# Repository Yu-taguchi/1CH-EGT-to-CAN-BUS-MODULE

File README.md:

# 1CH EGT TO CAN BUS モジュール

これは 1 チャンネル EGT ボードです。
このボードは、アフター製 エンジン コントロール ユニットと組み合わせて使用​​し、排気ガス温度を測定することを目的としています。
PCB は、1つの MAX31855 チップと ATMEGA328P に基づいています。
使用するセンサーは、ミニ K タイプ サーモカップル コネクタを備えた K タイプ EGT センサーである必要があります。

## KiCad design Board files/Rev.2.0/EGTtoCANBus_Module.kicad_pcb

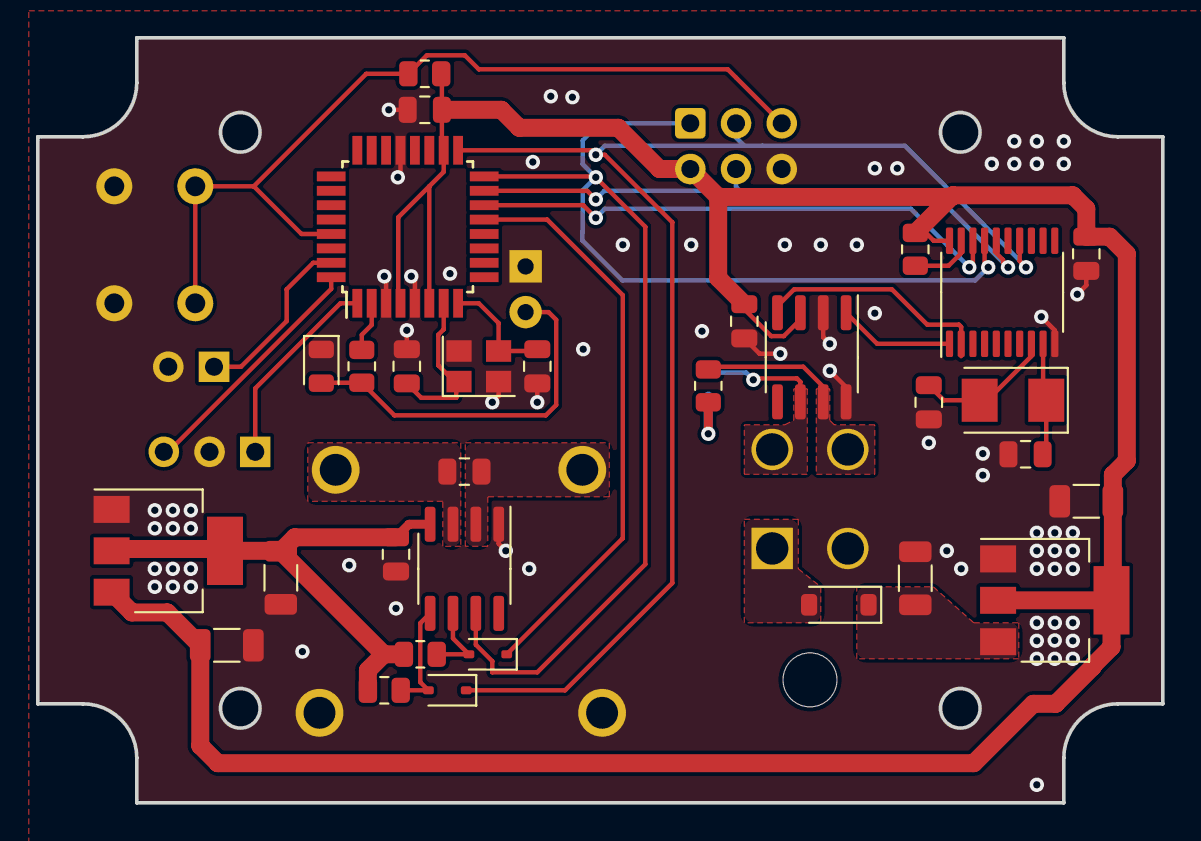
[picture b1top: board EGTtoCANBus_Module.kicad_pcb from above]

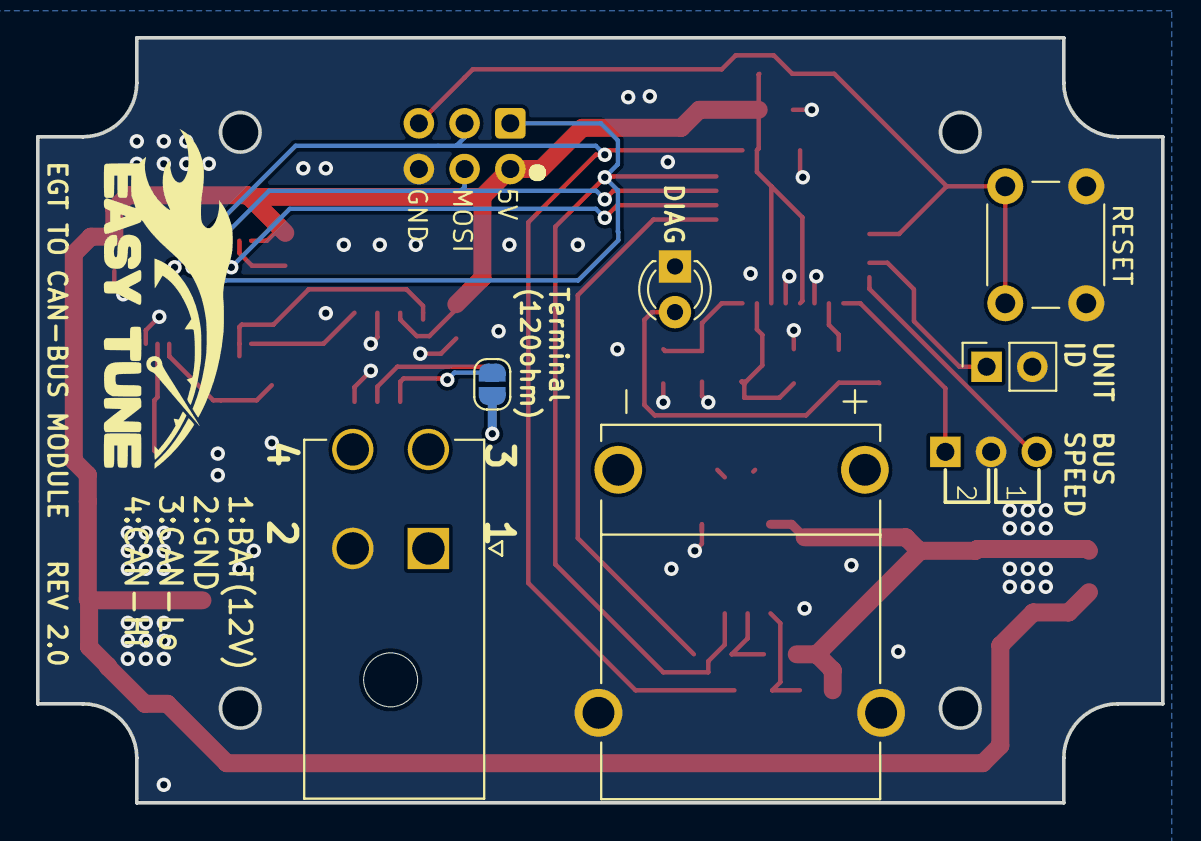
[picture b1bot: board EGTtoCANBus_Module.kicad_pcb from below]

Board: 2 copper layers, 62.5 x 42.5 mm, 39 parts (8 on the bottom side), 30 nets.

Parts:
C1, C2, C3, C8, C11: 0.1uF; C_0805_2012Metric
C4, C5, C6, C7: 10uF; C_1206_3216Metric
C9, C10, C12, C13: 22pF; C_0805_2012Metric
D1: LED; LED_D3.0mm
D2, D4: 1N4148WS; D_SOD-323
D3: D_Schottky; D_SOD-123
D5: LED; LED_0805_2012Metric
J1: AVR-ISP-6; IDC-Header_2x03_P2.54mm_Vertical
J2: 39-30-1040; MOLEX_39-30-1040
J3: PCC-SMP-V-K-5; OMEGA_PCC-SMP-K-5
JP1: SolderJumper; SolderJumper-2_P1.3mm_Open_RoundedPad1.0x1.5mm
JP2: Jumper_3_Open; PinSocket_1x03_P2.54mm_Vertical
JP3: Jumper_2_Open; PinSocket_1x02_P2.54mm_Vertical
R1: 120; R_0805_2012Metric
R2, R3, R6: 10k; R_0805_2012Metric
R5, R7: 1k; R_0805_2012Metric
RESET: SW_Push; SW_PUSH_6mm
U1: ATmega328P-A; TQFP-32_7x7mm_P0.8mm
U2: MCP2515-I; TSSOP-20_4.4x6.5mm_P0.65mm
U3: AMS1117-5.0; SOT-223-3_TabPin2
U5: AMS1117-3.3; SOT-223-3_TabPin2
U7: MAX31855KASA; SOIC-8_3.9x4.9mm_P1.27mm
U9: TJA1044T; SOIC-8_3.9x4.9mm_P1.27mm
Y2: 8MHz; Crystal_SMD_5032-2Pin_5.0x3.2mm
Y3: 16MHz; Crystal_SMD_3225-4Pin_3.2x2.5mm

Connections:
+3.3V: C3.1, C7.1, R2.1, R6.1, U5.2 (VO), U7.4 (V_CC)
+5V: C1.1, C2.1, C5.1, C6.1, C11.1, J1.2 (VCC), R3.1, R5.1, U1.4 (VCC), U1.6 (VCC), U1.18 (AVCC), U2.20 (VDD), U3.2 (VO), U5.3 (VI), U9.3 (VCC)
CANH: J2.4, R1.1, U9.7 (CANH)
CANL: J2.3, JP1.1 (A), U9.6 (CANL)
CS1: U1.14 (PB2), U2.18 (~CS)
CS2: D4.1 (K), U1.13 (PB1)
GND: C1.2, C2.2, C3.2, C4.2, C5.2, C6.2, C7.2, C9.2, C10.2, C11.2, C12.2, C13.2, D1.1 (K), D5.1 (K), J1.6 (GND), J2.2, J3.S1 (SHIELD), J3.S2 (SHIELD), JP2.2 (C), JP3.2 (B), RESET.1, U1.3 (GND), U1.5 (GND), U1.21 (GND), U2.10 (VSS), U3.1 (GND), U5.1 (GND), U7.1 (GND), U9.2 (GND), U9.8 (S), Y3.2, Y3.4
MISO: J1.1 (MISO), U1.16 (PB4), U2.17 (SO), U7.7 (SO)
MOSI: J1.4 (MOSI), U1.15 (PB3), U2.16 (SI)
unnamed: D1.2 (A), D5.2 (A), R7.2
unnamed: D2.2 (A), R2.2, U7.5 (SCK)
unnamed: C4.1, D3.1 (K), U3.3 (VI)
unnamed: D4.2 (A), R6.2, U7.6 (~CS)
unnamed: C8.1, J3.N (NEG), U7.2 (T-)
unnamed: C8.2, J3.P (POS), U7.3 (T+)
unnamed: JP1.2 (B), R1.2
unnamed: JP2.1 (A), U1.1 (PD3)
unnamed: JP2.3 (B), U1.32 (PD2)
unnamed: JP3.1 (A), U1.31 (PD1)
unnamed: R7.1, U1.2 (PD4)
unnamed: C12.1, U1.7 (XTAL1/PB6), Y3.1
unnamed: C13.1, U1.8 (XTAL2/PB7), Y3.3
unnamed: C10.1, U2.9 (OSC1), Y2.1
unnamed: C9.1, U2.8 (OSC2), Y2.2
unnamed: U2.2 (RXCAN), U9.4 (RXD)
unnamed: U2.1 (TXCAN), U9.1 (TXD)
unnamed: R3.2, U2.19 (~RESET)
RST: J1.5 (~RST), R5.2, RESET.2, U1.29 (~RESET/PC6)
SCK: D2.1 (K), J1.3 (SCK), U1.17 (PB5), U2.14 (SCK)
VCC: D3.2 (A), J2.1

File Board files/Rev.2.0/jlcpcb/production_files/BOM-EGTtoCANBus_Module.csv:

Comment,Designator,Footprint,LCSC
8MHz,Y2,Crystal_SMD_5032-2Pin_5.0x3.2mm,C115962
10uF,"C4,C5,C6,C7",C_1206_3216Metric,C13585
16MHz,Y3,Crystal_SMD_3225-4Pin_3.2x2.5mm,C13738
ATmega328P-A,U1,TQFP-32_7x7mm_P0.8mm,C14877
10k,"R2,R3,R6",R_0805_2012Metric,C17414
120,R1,R_0805_2012Metric,C17437
1k,"R5,R7",R_0805_2012Metric,C17513
22pF,"C10,C12,C13,C9",C_0805_2012Metric,C1804
1N4148WS,"D2,D4",D_SOD-323,C2128
LED,"D1,D5",LED_D3.0mm,C2297
0.1uF,"C1,C11,C2,C3,C8",C_0805_2012Metric,C49678
MAX31855KASA,U7,SOIC-8_3.9x4.9mm_P1.27mm,C52028
TJA1044T,U9,SOIC-8_3.9x4.9mm_P1.27mm,C520388
MCP2515-I,U2,TSSOP-20_4.4x6.5mm_P0.65mm,C5250735
AMS1117-3.3,U5,SOT-223-3_TabPin2,C6186
AMS1117-5.0,U3,SOT-223-3_TabPin2,C6187
D_Schottky,D3,D_SOD-123,C8598
Jumper_2_Open,JP3,PinSocket_1x02_P2.54mm_Vertical,
Jumper_3_Open,JP2,PinSocket_1x03_P2.54mm_Vertical,
SolderJumper,JP1,SolderJumper-2_P1.3mm_Open_RoundedPad1.0x1.5mm,
39-30-1040,J2,MOLEX_39-30-1040,
PCC-SMP-V-K-5,J3,OMEGA_PCC-SMP-K-5,
AVR-ISP-6,J1,IDC-Header_2x03_P2.54mm_Vertical,

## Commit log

2025-01-19 Create LINK G4X instructions
2025-01-19 Create Read
2025-01-19 Create test
2025-02-02 Update 1ch_EGT_to_CAN_BUS_MODULE.ino
    基準接点温度計測、および故障診断機能を追加
2025-03-16 Create try1
2025-03-16 Create ree
2025-03-16 Create tes
2025-05-23 Create a
